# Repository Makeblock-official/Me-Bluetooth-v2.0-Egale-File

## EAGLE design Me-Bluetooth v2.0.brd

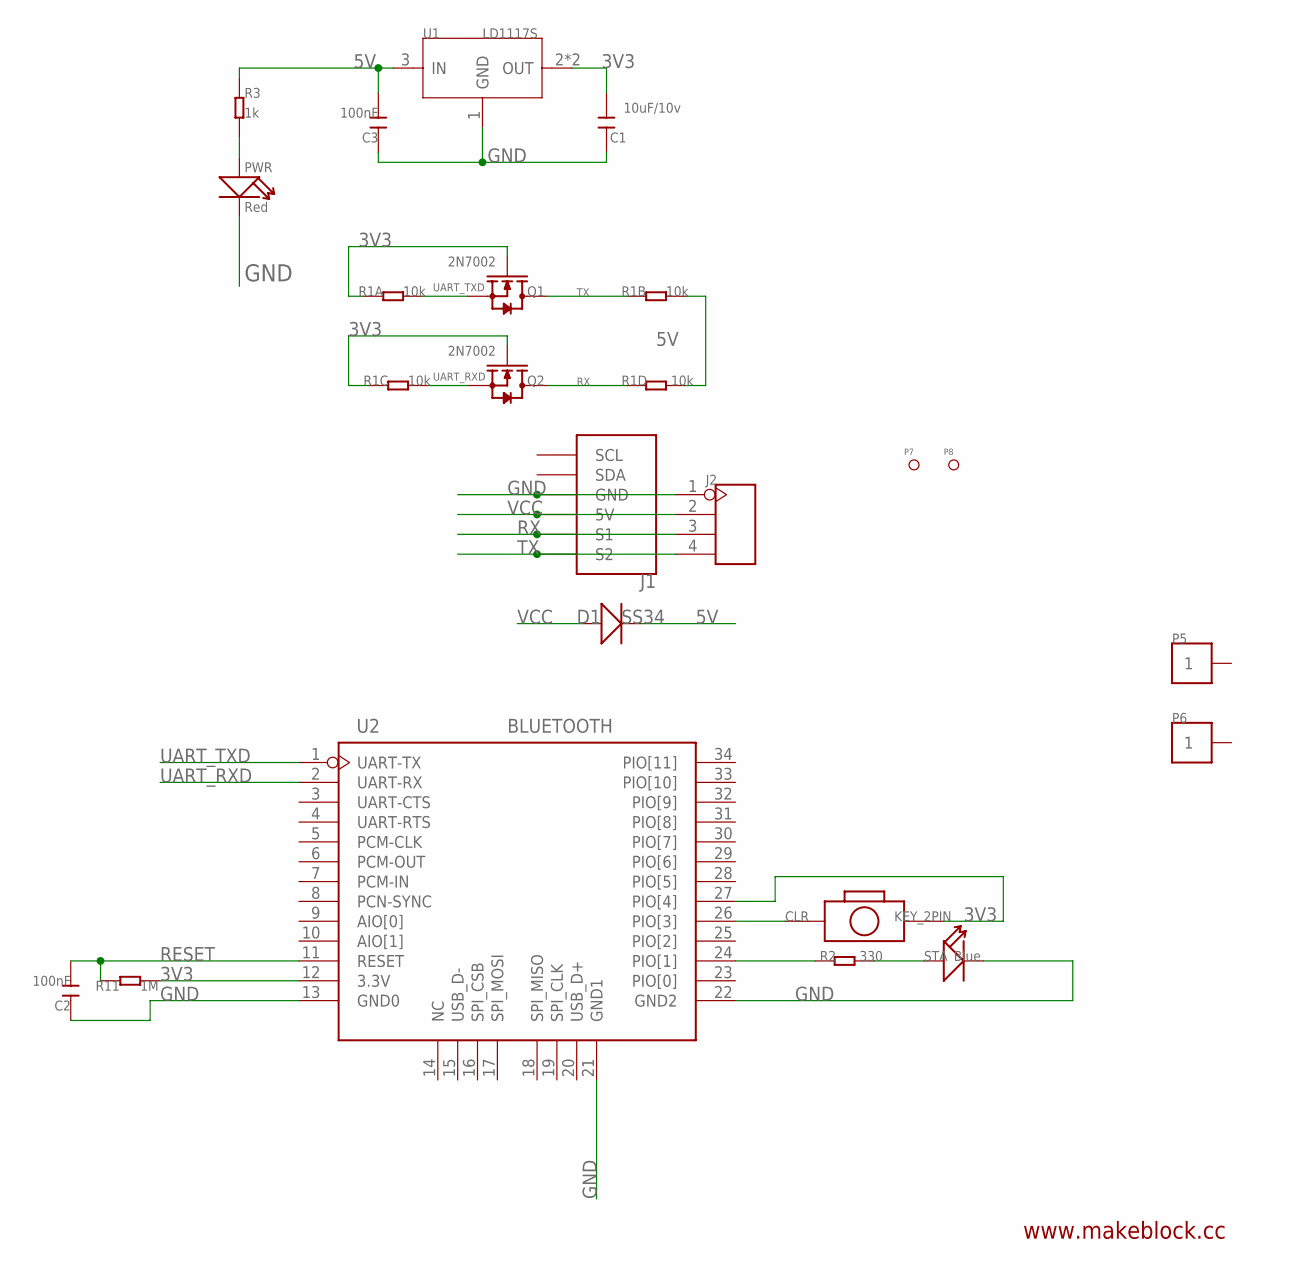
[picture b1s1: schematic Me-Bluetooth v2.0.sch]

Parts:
C1: 10uF/10v; 0603
C2, C3: 100nF; 0603
CLR: KEY_2PIN
D1: SS34; D2010
J1: RJ11-6P6C-DIGI; RJ11-6P6C
J2: HEADER-4P-60/35MIL; 4P-65/35MIL
P5, P6: PAD-1P-4MM; HOLE-01
P7, P8: PAD-MARK; ROUND-MARK-1.0
PWR: Red; LED-0603
Q1, Q2: 2N7002
R1: 10k; 1206-8-3.3X2.4
R2: 330; 0603
R3: 1k; 0603
R11: 1M; 0603
STA: Blue; LED-0603
U1: LD1117S; SOT-223
U2: BLUETOOTH

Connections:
3V3: C1.2, CLR.P$2 (2), Q1.1 (G), Q2.1 (G), R1.1, R1.3 (1), R11.2, U1.2 (OUT), U1.TER (OUT), U2.12 (3.3V), U2.27 (PIO[4])
5V: C3.2, D1.-, R1.5 (2), R1.7 (2), R3.1, U1.3 (IN)
GND: C1.1, C2.1, C3.1, J1.3 (GND), J2.1, PWR.-, STA.-, U1.1 (GND), U2.13 (GND0), U2.21 (GND1), U2.22 (GND2)
unnamed: R2.2, STA.+
unnamed: CLR.1, U2.26 (PIO[3])
unnamed: PWR.+, R3.2
unnamed: R2.1, U2.24 (PIO[1])
RESET: C2.2, R11.1, U2.11 (RESET)
RX: J1.5 (S1), J2.3, Q2.3 (D), R1.4 (1)
TX: J1.6 (S2), J2.4, Q1.3 (D), R1.2 (1)
UART_RXD: Q2.2 (S), R1.6 (2), U2.2 (UART-RX)
UART_TXD: Q1.2 (S), R1.8 (2), U2.1 (UART-TX)
VCC: D1.+, J1.4 (5V), J2.2

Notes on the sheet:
www.makeblock.cc

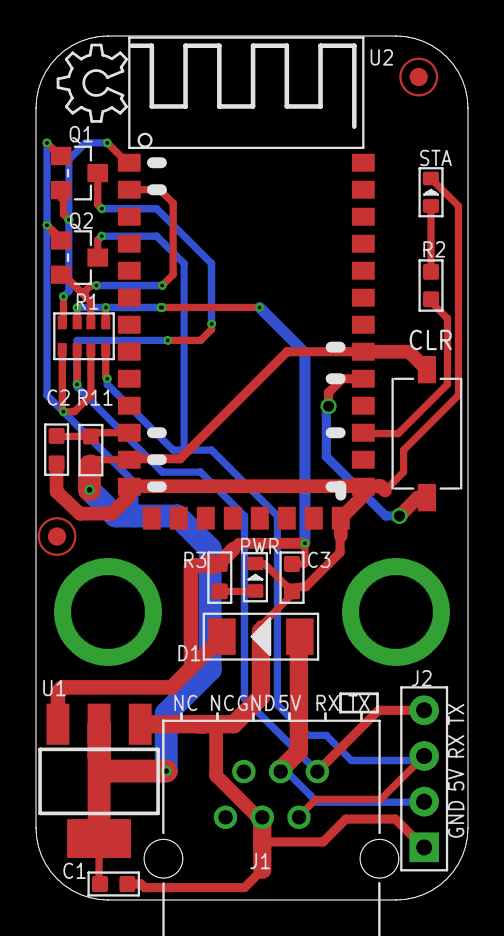
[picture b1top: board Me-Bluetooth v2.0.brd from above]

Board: 2 copper layers, 24.0 x 48.0 mm, 23 parts (1 on the bottom side), 13 nets.

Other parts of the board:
U$1: LOGO-3/2
U$2: OSHW_6X150_NOTEXT

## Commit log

2013-08-27 PCB files
